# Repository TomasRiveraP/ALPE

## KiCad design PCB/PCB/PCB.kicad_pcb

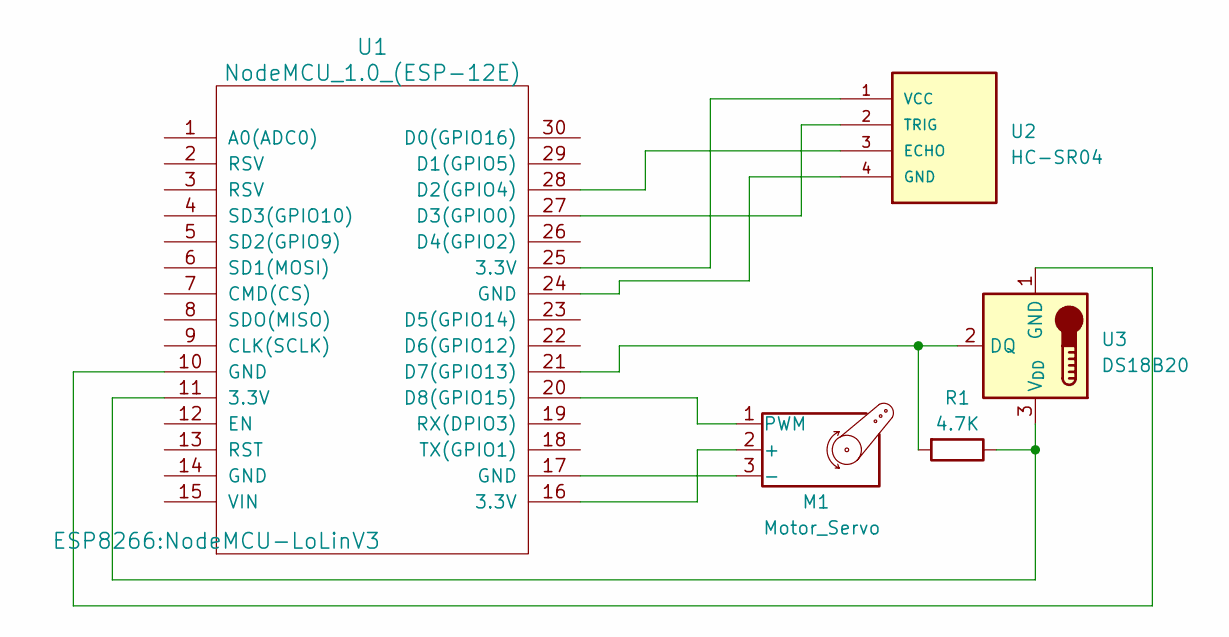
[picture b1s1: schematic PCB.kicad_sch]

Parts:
M1: Motor_Servo; PinHeader_1x03_P2.00mm_Vertical
R1: 4.7K; R_Axial_DIN0204_L3.6mm_D1.6mm_P5.08mm_Horizontal
U1: NodeMCU_1.0_(ESP-12E); NodeMCU-LoLinV3
U2: HC-SR04; XCVR_HC-SR04
U3: DS18B20; TO-92_Inline

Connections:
unnamed: M1.2 (+), U1.16 (3.3V)
unnamed: M1.3 (-), U1.17 (GND)
unnamed: M1.1 (PWM), U1.20 (D8(GPIO15))
unnamed: U1.28 (D2(GPIO4)), U2.3 (ECHO)
unnamed: U1.27 (D3(GPIO0)), U2.2 (TRIG)
unnamed: R1.2, U1.21 (D7(GPIO13)), U3.2 (DQ)
unnamed: U1.24 (GND), U2.4 (GND)
unnamed: U1.25 (3.3V), U2.1 (VCC)
unnamed: U1.10 (GND), U3.1 (GND)
unnamed: R1.1, U1.11 (3.3V), U3.3 (V_{DD})

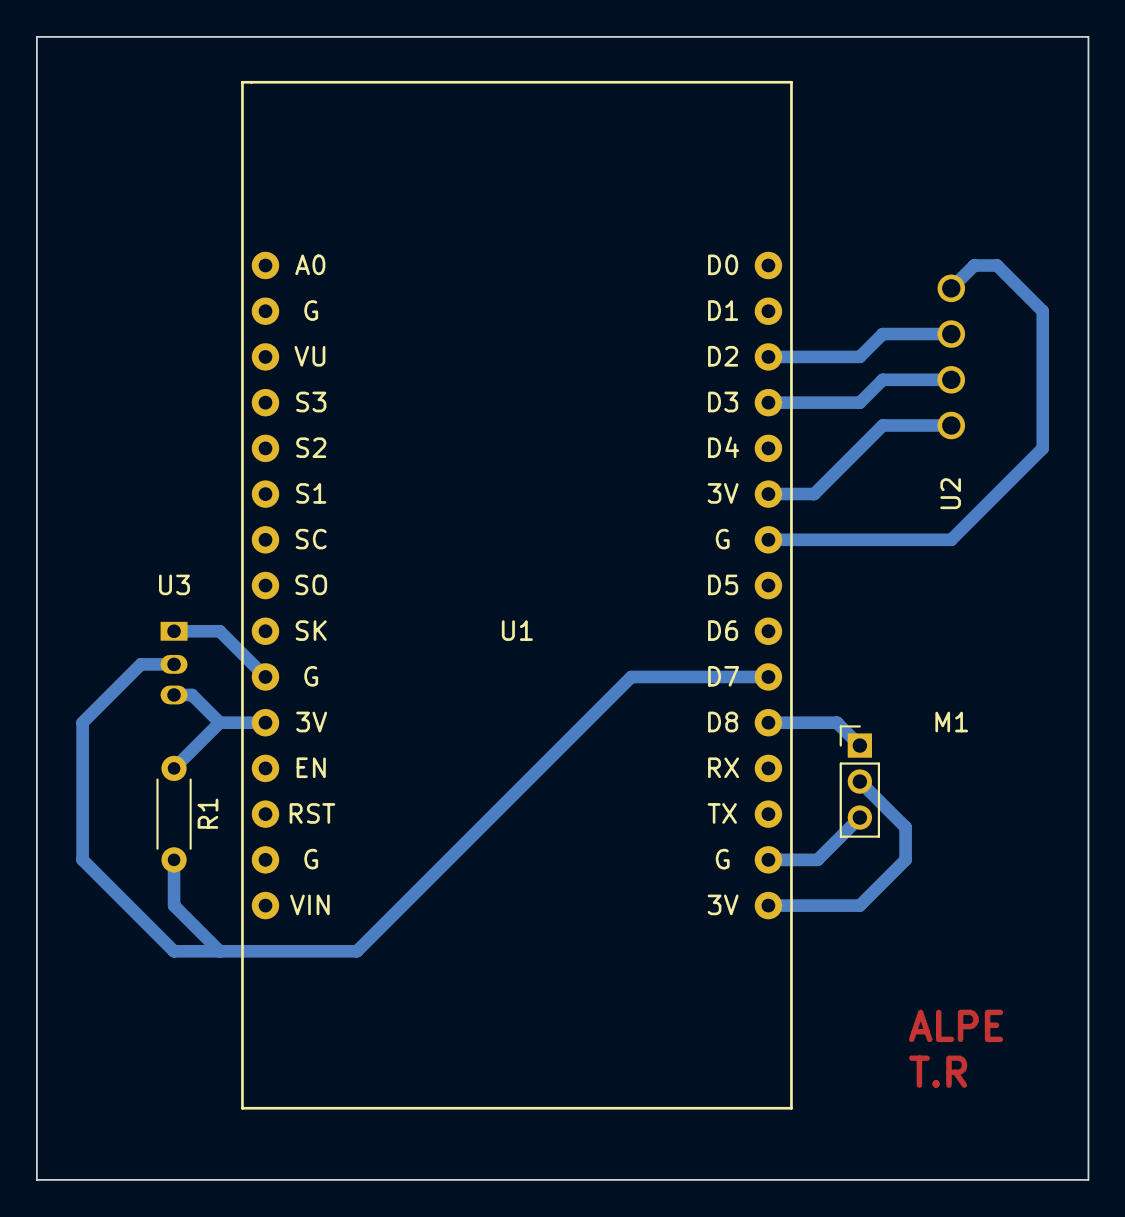
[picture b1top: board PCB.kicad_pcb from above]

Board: 2 copper layers, 58.4 x 63.5 mm, 5 parts (0 on the bottom side), 10 nets.

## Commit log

2023-10-27 version 1.01
